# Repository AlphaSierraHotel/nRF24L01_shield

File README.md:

# README

The basis of this project is not mine but is derived from the work of the MySensors forum user, [NeverDie](https://forum.mysensors.org/user/neverdie). The [related forum thread](https://forum.mysensors.org/topic/11954/most-reliable-best-radio) is a discussion and progression of building a test platform for testing RF radio modules, as well as a discussion of testing those radio modules.  

This repository is meant merely as a way to backup my work and to share my copy/version of the pieces of the project that I'm interested in.  It is also a minor test of using git with KiCad files.

I considered using [this article](https://medium.com/inventhub/better-manage-kicad-projects-using-git-8d06e1310af8) as a guideline for building this repository but decided that it was more structure than was needed for this project.  Linking it here for posterity and my own future reference.

You can find NeverDie's [original schematic](assets/schematic_v001.pdf) in the assets folder.

Here is what this particular radio module shield board looks like.

Top

and Bottom

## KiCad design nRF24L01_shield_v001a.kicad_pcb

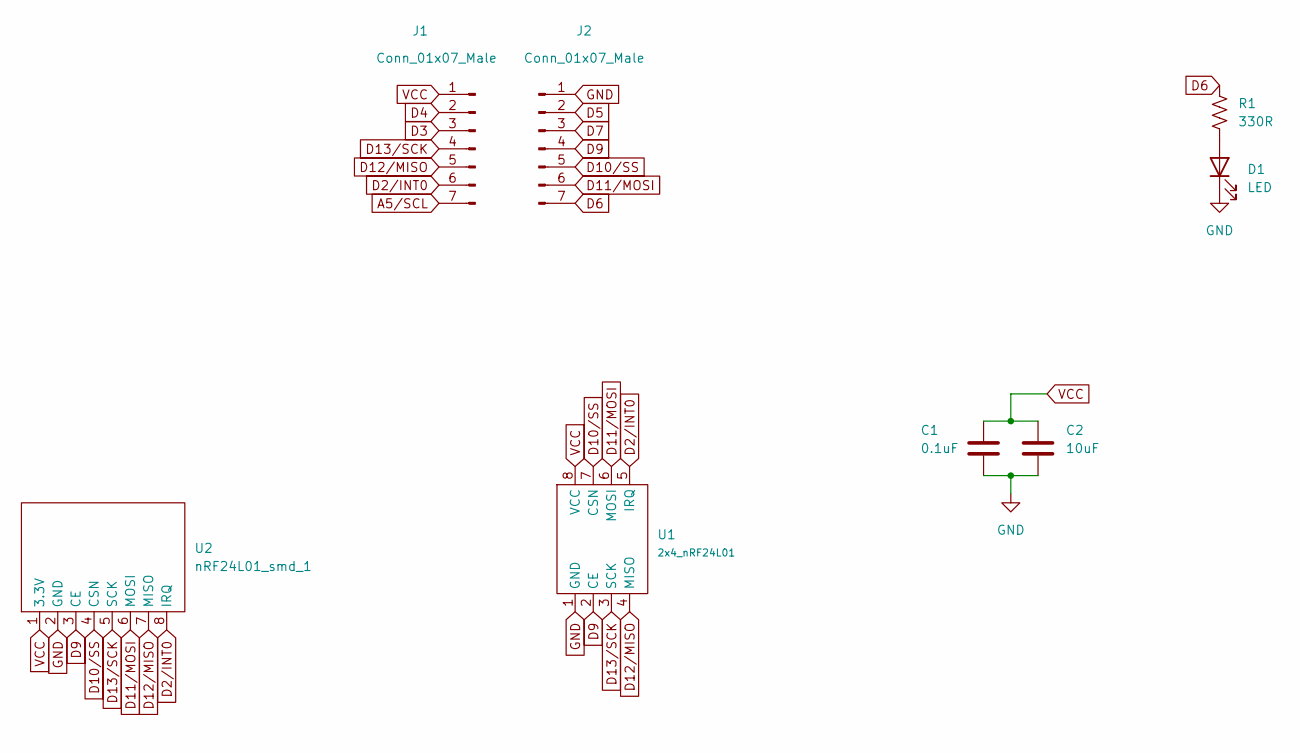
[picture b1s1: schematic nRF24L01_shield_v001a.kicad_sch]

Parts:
C1: 0.1uF; C_0805_2012Metric_Pad1.18x1.45mm_HandSolder
C2: 10uF; C_0805_2012Metric_Pad1.18x1.45mm_HandSolder
D1: LED; LED_0805_2012Metric_Pad1.15x1.40mm_HandSolder
J1, J2: Conn_01x07_Male; PinHeader_1x07_P2.54mm_Vertical
R1: 330R; R_0805_2012Metric_Pad1.20x1.40mm_HandSolder
U1: 2x4_nRF24L01; 2X4_nRF24L01
U2: nRF24L01_smd_1; nRF24L01_smd

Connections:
A5/SCL: J1.7
D2/INT0: J1.6, U1.5 (IRQ), U2.8 (IRQ)
D3: J1.3
D4: J1.2
D5: J2.2
D6: J2.7, R1.1
D7: J2.3
D9: J2.4, U1.2 (CE), U2.3 (CE)
D10/SS: J2.5, U1.7 (CSN), U2.4 (CSN)
D11/MOSI: J2.6, U1.6 (MOSI), U2.6 (MOSI)
D12/MISO: J1.5, U1.4 (MISO), U2.7 (MISO)
D13/SCK: J1.4, U1.3 (SCK), U2.5 (SCK)
GND: C1.2, C2.2, D1.1 (K), J2.1, U1.1 (GND), U2.2 (GND)
unnamed: D1.2 (A), R1.2
VCC: C1.1, C2.1, J1.1, U1.8 (VCC), U2.1 (3.3V)

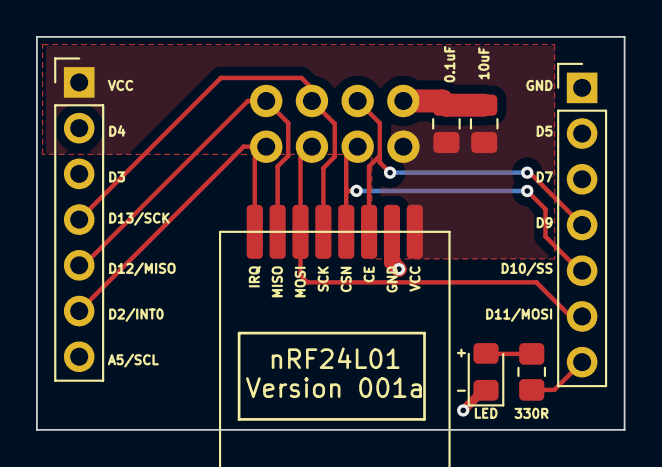
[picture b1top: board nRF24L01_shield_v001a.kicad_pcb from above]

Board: 2 copper layers, 32.7 x 21.8 mm, 8 parts (0 on the bottom side), 10 nets.

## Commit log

2022-06-22 Add archive of the project to assets
2022-06-22 Update README.md
    Grammar (police)
